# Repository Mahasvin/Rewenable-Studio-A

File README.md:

# Rewenable-Studio-A
Working Full Bridge Converter using MOSFETs and a IR2103 IC chip

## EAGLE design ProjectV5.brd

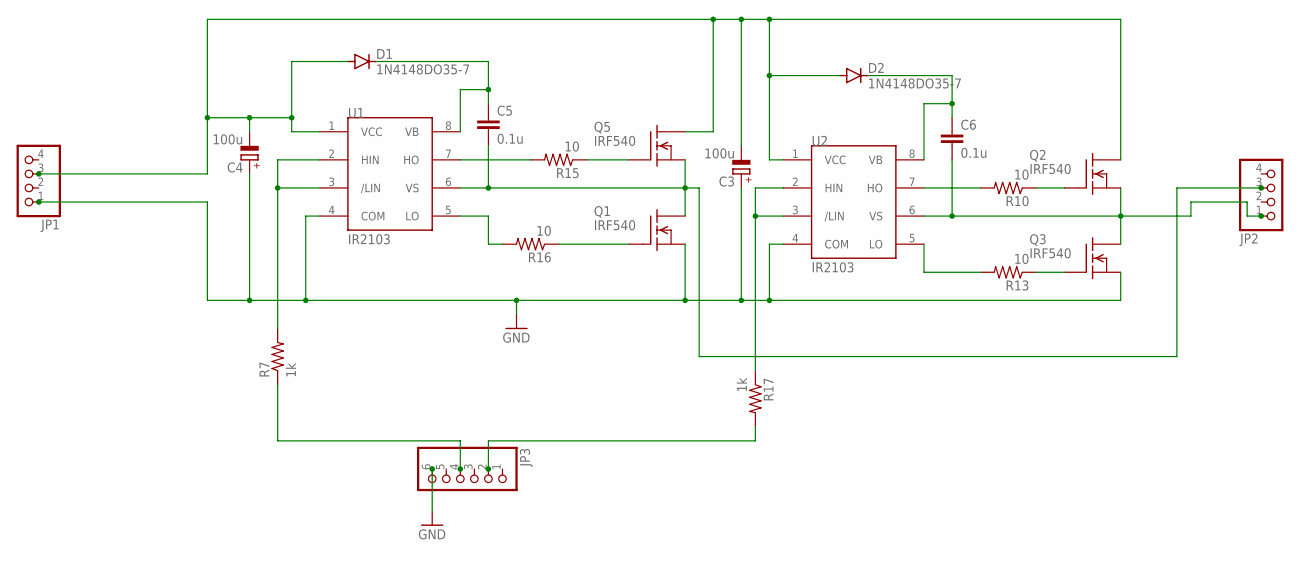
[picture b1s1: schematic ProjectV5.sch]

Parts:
C3, C4: 100u; E2,5-6
C5, C6: 0.1u; C050-030X075
D1, D2: 1N4148DO35-7; DO35-7
JP1, JP2: PINHD-1X4; 1X04
JP3: PINHD-1X6; 1X06
Q1, Q2, Q3, Q5: IRF540; TO220
R7, R17: 1k; 0309/12
R10, R13, R15, R16: 10; 0309/12
U1, U2: IR2103; DIL08

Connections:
GND: C3.+, C4.+, JP1.1, JP3.6, Q1.3 (S), Q3.3 (S), U1.4 (COM), U2.4 (COM)
LEGA: C5.2, JP2.3, Q1.2 (D), Q5.3 (S), U1.6 (VS)
LEGB: C6.2, JP2.1, Q2.3 (S), Q3.2 (D), U2.6 (VS)
unnamed: Q3.1 (G), R13.1
unnamed: Q2.1 (G), R10.1
unnamed: R10.2, U2.7 (HO)
unnamed: R13.2, U2.5 (LO)
unnamed: R15.2, U1.7 (HO)
unnamed: Q1.1 (G), R16.1
unnamed: R16.2, U1.5 (LO)
unnamed: R17.1, U2.2 (HIN), U2.3 (/LIN)
unnamed: Q5.1 (G), R15.1
unnamed: JP3.2, R17.2
unnamed: JP3.4, R7.1
unnamed: R7.2, U1.2 (HIN), U1.3 (/LIN)
VB: C5.1, C6.1, D1.C, D2.C, U1.8 (VB), U2.8 (VB)
VCC: C3.-, C4.-, D1.A, D2.A, JP1.3, Q2.2 (D), Q5.2 (D), U1.1 (VCC), U2.1 (VCC)

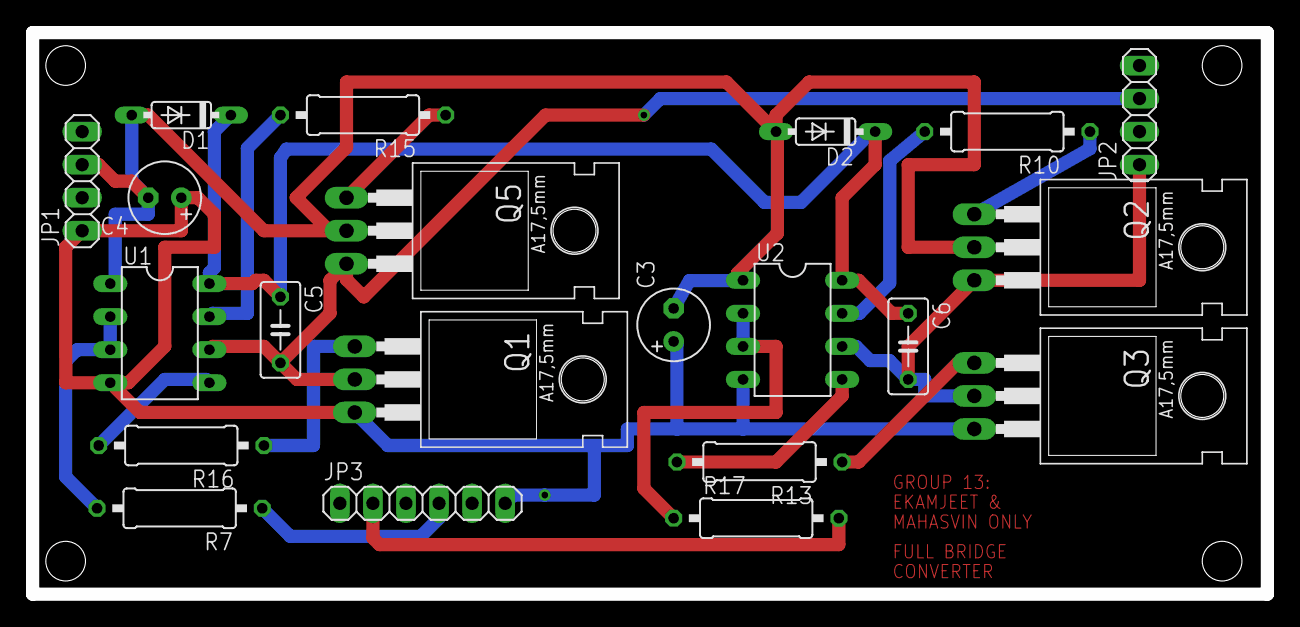
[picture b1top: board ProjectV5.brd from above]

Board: 2 copper layers, 94.9 x 43.2 mm, 21 parts (0 on the bottom side), 17 nets.

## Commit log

2022-01-25 Full Bridge Converter Autodesk Eagle
    For washing Machine Project
2022-01-25 Picture of PCB
